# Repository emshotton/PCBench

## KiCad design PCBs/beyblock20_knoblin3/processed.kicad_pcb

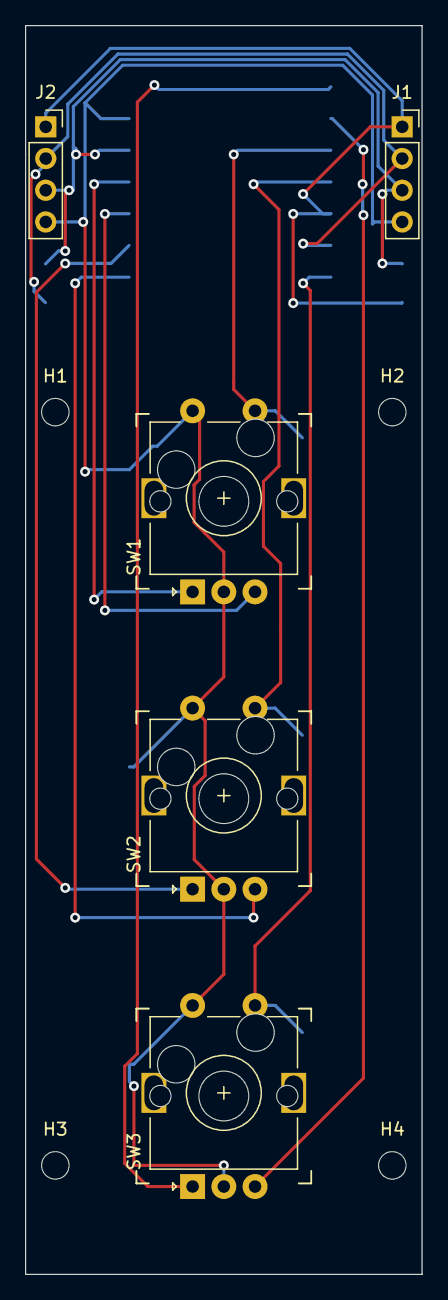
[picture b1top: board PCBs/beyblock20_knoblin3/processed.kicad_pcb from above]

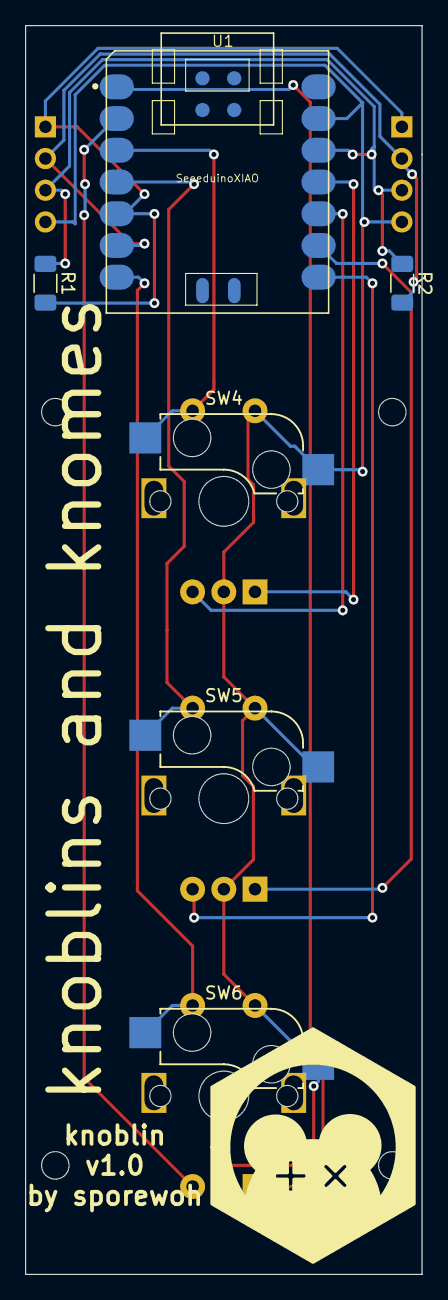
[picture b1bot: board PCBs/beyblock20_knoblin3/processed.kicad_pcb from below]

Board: 2 copper layers, 31.8 x 100.0 mm, 15 parts (3 on the bottom side), 13 nets.

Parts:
H1, H2, H3, H4: MountingHole; MountingHole_2.2mm_M2_DIN965
J1: Conn_01x04_Male; PinSocket_1x04_P2.54mm_Vertical
J2: Conn_01x04_Female; PinSocket_1x04_P2.54mm_Vertical
R1, R2: R; R_1206_3216Metric_Pad1.30x1.75mm_HandSolder
SW1, SW2, SW3: RotaryEncoder_Switch; RotaryEncoder_Alps_EC11E-Switch_Vertical_H20mm
SW4, SW5, SW6: SW_SPST; Kailh_socket_MX
U1: SeeeduinoXIAO; Seeeduino XIAO-MOUDLE14P-2.54-21X17.8MM

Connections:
3v3: J1.3, J2.3, R1.1, R2.1, U1.12 (3V3)
a1: SW1.A, U1.11 (PA6_A10_D10_MOSI)
a2: SW2.A, U1.9 (PA7_A8_D8_SCK)
a3: SW3.A, U1.1 (PA02_A0_D0)
b1: SW1.B, U1.10 (PA5_A9_D9_MISO)
b2: SW2.B, U1.8 (PB09_A7_D7_RX)
b3: SW3.B, U1.2 (PA4_A1_D1)
gnd: J1.4, J2.4, SW1.C, SW1.S2, SW2.C, SW2.S2, SW3.C, SW3.S2, SW4.2 (B), SW5.2 (B), SW6.2 (B), U1.13 (GND)
key1: SW1.S1, SW4.1 (A), U1.3 (PA10_A2_D2)
key2: SW2.S1, SW5.1 (A), U1.4 (PA11_A3_D3)
key3: SW3.S1, SW6.1 (A), U1.7 (PB08_A6_D6_TX)
scl: J1.2, J2.2, R2.2, U1.6 (PA9_A5_D5_SCL)
sda: J1.1, J2.1, R1.2, U1.5 (PA8_A4_D4_SDA)

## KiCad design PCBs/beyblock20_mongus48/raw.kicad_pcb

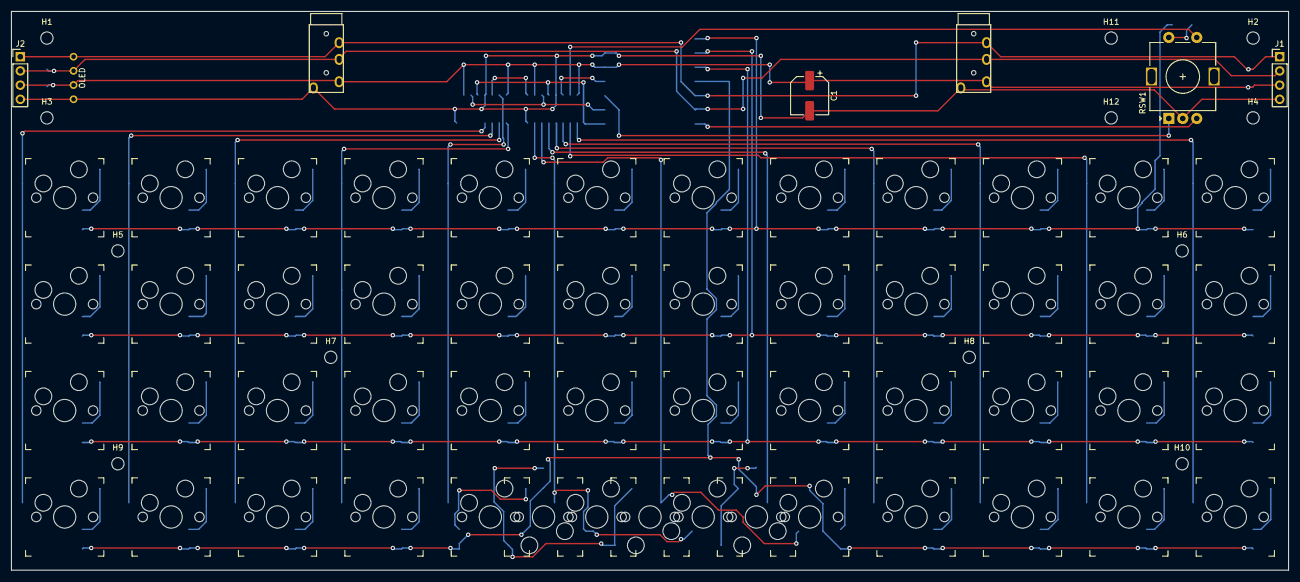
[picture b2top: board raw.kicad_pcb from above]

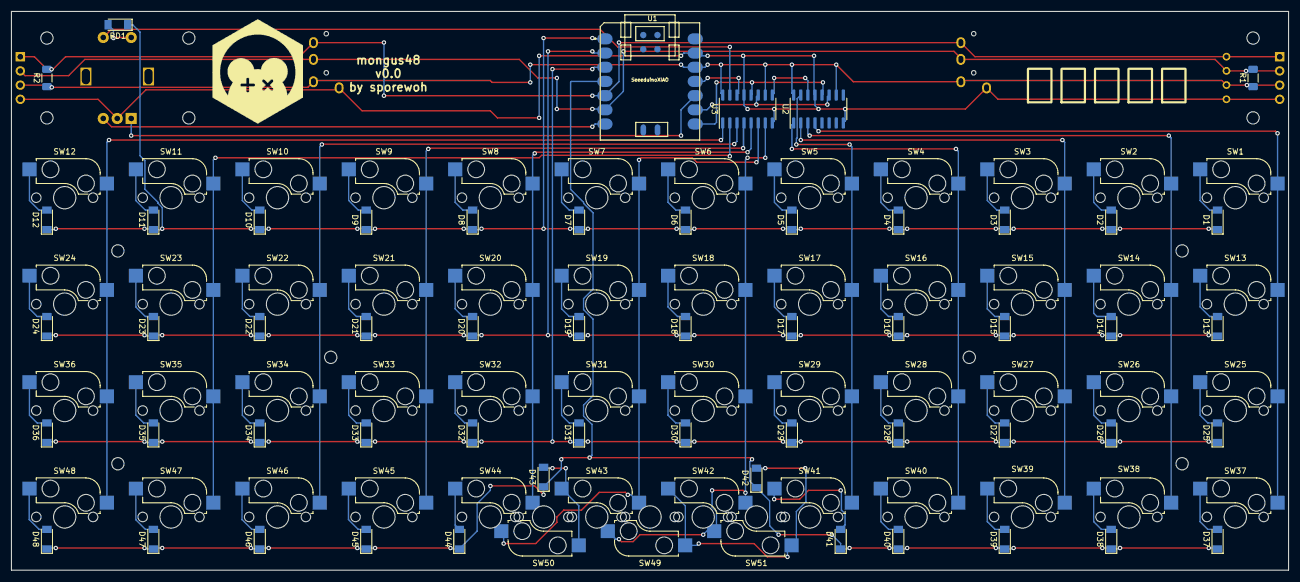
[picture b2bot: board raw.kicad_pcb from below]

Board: 2 copper layers, 228.6 x 100.0 mm, 124 parts (54 on the bottom side), 76 nets.

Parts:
C1: C_Polarized_US; CP_Elec_6.3x7.7
D1, D2, D3, D4, D5, D6, D7, D8, D9, D10, D11, D12, D13, D14, D15, D16, D17, D18, D19, D20, D21, D22, D23, D24, D25, D26, D27, D28, D29, D30, D31, D32, D33, D34, D35, D36, D37, D38, D39, D40, D41, D42, D43, D44, D45, D46, D47, D48: LL4148; D_MiniMELF
H1, H2, H3, H4, H5, H6, H7, H8, H9, H10, H11, H12: MountingHole; MountingHole_2.2mm_M2_DIN965
J1: Conn_01x04_Male; PinHeader_1x04_P2.54mm_Vertical
J2: Conn_01x04_Female; PinHeader_1x04_P2.54mm_Vertical
OL1: OLED; OLED_v2
R1, R2: R; R_1206_3216Metric_Pad1.30x1.75mm_HandSolder
RD1: LL4148; D_MiniMELF
RSW1: RotaryEncoder_Switch; RotaryEncoder_Alps_EC11E-Switch_Vertical_H20mm
SW1, SW2, SW3, SW4, SW5, SW6, SW7, SW8, SW9, SW10, SW11, SW12: locked; Kailh_socket_MX
SW13, SW14, SW15, SW16, SW17, SW18, SW19, SW20, SW21, SW22, SW23, SW24, SW25, SW26, SW27, SW28, SW29, SW30, SW31, SW32, SW33, SW34, SW35, SW36, SW37, SW38, SW39, SW40, SW41, SW42, SW43, SW44, SW45, SW46, SW47, SW48, SW49, SW50, SW51: SW_SPST; Kailh_socket_MX
U1: SeeeduinoXIAO; Seeeduino XIAO-MOUDLE14P-2.54-21X17.8MM
U2, U3: 74HC595; SOP-16_3.9x9.9mm_P1.27mm
U5: TRRS; TRRS-PJ-320A
locked: TRRS; TRRS-PJ-320A

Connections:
3v3: C1.1, J1.3, J2.3, OL1.3 (VCC), R1.1, R2.1, U1.12 (3V3), U2.10 (~SRCLR), U2.16 (VCC), U3.10 (~SRCLR), U3.16 (VCC), U5.2 (TIP), locked.2 (TIP)
unnamed: D1.2 (A), SW1.1 (A)
unnamed: D2.2 (A), SW2.1 (A)
unnamed: D3.2 (A), SW3.1 (A)
unnamed: D4.2 (A), SW4.1 (A)
unnamed: D5.2 (A), SW5.1 (A)
unnamed: D6.2 (A), SW6.1 (A)
unnamed: D7.2 (A), SW7.1 (A)
unnamed: D8.2 (A), SW8.1 (A)
unnamed: D9.2 (A), SW9.1 (A)
unnamed: D10.2 (A), SW10.1 (A)
unnamed: D11.2 (A), SW11.1 (A)
unnamed: D12.2 (A), SW12.1 (A)
unnamed: D13.2 (A), SW13.1 (A)
unnamed: D14.2 (A), SW14.1 (A)
unnamed: D15.2 (A), SW15.1 (A)
unnamed: D16.2 (A), SW16.1 (A)
unnamed: D17.2 (A), SW17.1 (A)
unnamed: D18.2 (A), SW18.1 (A)
unnamed: D19.2 (A), SW19.1 (A)
unnamed: D20.2 (A), SW20.1 (A)
unnamed: D21.2 (A), SW21.1 (A)
unnamed: D22.2 (A), SW22.1 (A)
unnamed: D23.2 (A), SW23.1 (A)
unnamed: D24.2 (A), SW24.1 (A)
unnamed: D25.2 (A), SW25.1 (A)
unnamed: D26.2 (A), SW26.1 (A)
unnamed: D27.2 (A), SW27.1 (A)
unnamed: D28.2 (A), SW28.1 (A)
unnamed: D29.2 (A), SW29.1 (A)
unnamed: D30.2 (A), SW30.1 (A)
unnamed: D31.2 (A), SW31.1 (A)
unnamed: D32.2 (A), SW32.1 (A)
unnamed: D33.2 (A), SW33.1 (A)
unnamed: D34.2 (A), SW34.1 (A)
unnamed: D35.2 (A), SW35.1 (A)
unnamed: D36.2 (A), SW36.1 (A)
unnamed: D37.2 (A), SW37.1 (A)
unnamed: D38.2 (A), SW38.1 (A)
unnamed: D39.2 (A), SW39.1 (A)
unnamed: D40.2 (A), SW40.1 (A)
unnamed: D41.2 (A), SW41.1 (A)
unnamed: D42.2 (A), SW42.1 (A), SW49.1 (A), SW51.1 (A)
unnamed: D43.2 (A), SW43.1 (A), SW50.1 (A)
unnamed: D44.2 (A), SW44.1 (A)
unnamed: D45.2 (A), SW45.1 (A)
unnamed: D46.2 (A), SW46.1 (A)
unnamed: D47.2 (A), SW47.1 (A)
unnamed: D48.2 (A), SW48.1 (A)
unnamed: RD1.2 (A), RSW1.S2
unnamed: U2.14 (SER), U3.9 (QH')
col0: RSW1.S1, U3.15 (QA)
col1: SW12.2 (B), SW24.2 (B), SW36.2 (B), SW48.2 (B), U3.1 (QB)
col2: SW11.2 (B), SW23.2 (B), SW35.2 (B), SW47.2 (B), U3.2 (QC)
col3: SW10.2 (B), SW22.2 (B), SW34.2 (B), SW46.2 (B), U3.3 (QD)
col4: SW9.2 (B), SW21.2 (B), SW33.2 (B), SW45.2 (B), U3.4 (QE)
col5: SW8.2 (B), SW20.2 (B), SW32.2 (B), SW44.2 (B), U3.5 (QF)
col6: SW7.2 (B), SW19.2 (B), SW31.2 (B), SW43.2 (B), SW50.2 (B), U3.6 (QG)
col7: SW6.2 (B), SW18.2 (B), SW30.2 (B), SW42.2 (B), SW49.2 (B), SW51.2 (B), U3.7 (QH)
col8: SW5.2 (B), SW17.2 (B), SW29.2 (B), SW41.2 (B), U2.15 (QA)
col9: SW4.2 (B), SW16.2 (B), SW28.2 (B), SW40.2 (B), U2.1 (QB)
col10: SW3.2 (B), SW15.2 (B), SW27.2 (B), SW39.2 (B), U2.2 (QC)
col11: SW2.2 (B), SW14.2 (B), SW26.2 (B), SW38.2 (B), U2.3 (QD)
col12: SW1.2 (B), SW13.2 (B), SW25.2 (B), SW37.2 (B), U2.4 (QE)
gnd: C1.2, J1.4, J2.4, OL1.4 (GND), RSW1.C, U1.13 (GND), U2.8 (GND), U2.13 (~OE), U3.8 (GND), U3.13 (~OE), U5.1 (SLEEVE), locked.1 (SLEEVE)
io_cs: U1.8 (PB09_A7_D7_RX), U2.12 (RCLK), U3.12 (RCLK)
mosi: U1.11 (PA6_A10_D10_MOSI), U3.14 (SER)
pad_a: RSW1.A, U1.10 (PA5_A9_D9_MISO)
pad_b: RSW1.B, U1.7 (PB08_A6_D6_TX)
row0: D1.1 (K), D2.1 (K), D3.1 (K), D4.1 (K), D5.1 (K), D6.1 (K), D7.1 (K), D8.1 (K), D9.1 (K), D10.1 (K), D11.1 (K), D12.1 (K), RD1.1 (K), U1.1 (PA02_A0_D0)
row1: D13.1 (K), D14.1 (K), D15.1 (K), D16.1 (K), D17.1 (K), D18.1 (K), D19.1 (K), D20.1 (K), D21.1 (K), D22.1 (K), D23.1 (K), D24.1 (K), U1.2 (PA4_A1_D1)
row2: D25.1 (K), D26.1 (K), D27.1 (K), D28.1 (K), D29.1 (K), D30.1 (K), D31.1 (K), D32.1 (K), D33.1 (K), D34.1 (K), D35.1 (K), D36.1 (K), U1.3 (PA10_A2_D2)
row3: D37.1 (K), D38.1 (K), D39.1 (K), D40.1 (K), D41.1 (K), D42.1 (K), D43.1 (K), D44.1 (K), D45.1 (K), D46.1 (K), D47.1 (K), D48.1 (K), U1.4 (PA11_A3_D3)
sck: U1.9 (PA7_A8_D8_SCK), U2.11 (SRCLK), U3.11 (SRCLK)
scl: J1.2, J2.2, OL1.2 (SCL), R1.2, U1.6 (PA9_A5_D5_SCL), U5.3 (RING1), locked.3 (RING1)
sda: J1.1, J2.1, OL1.1 (SDA), R2.2, U1.5 (PA8_A4_D4_SDA), U5.4 (RING2), locked.4 (RING2)

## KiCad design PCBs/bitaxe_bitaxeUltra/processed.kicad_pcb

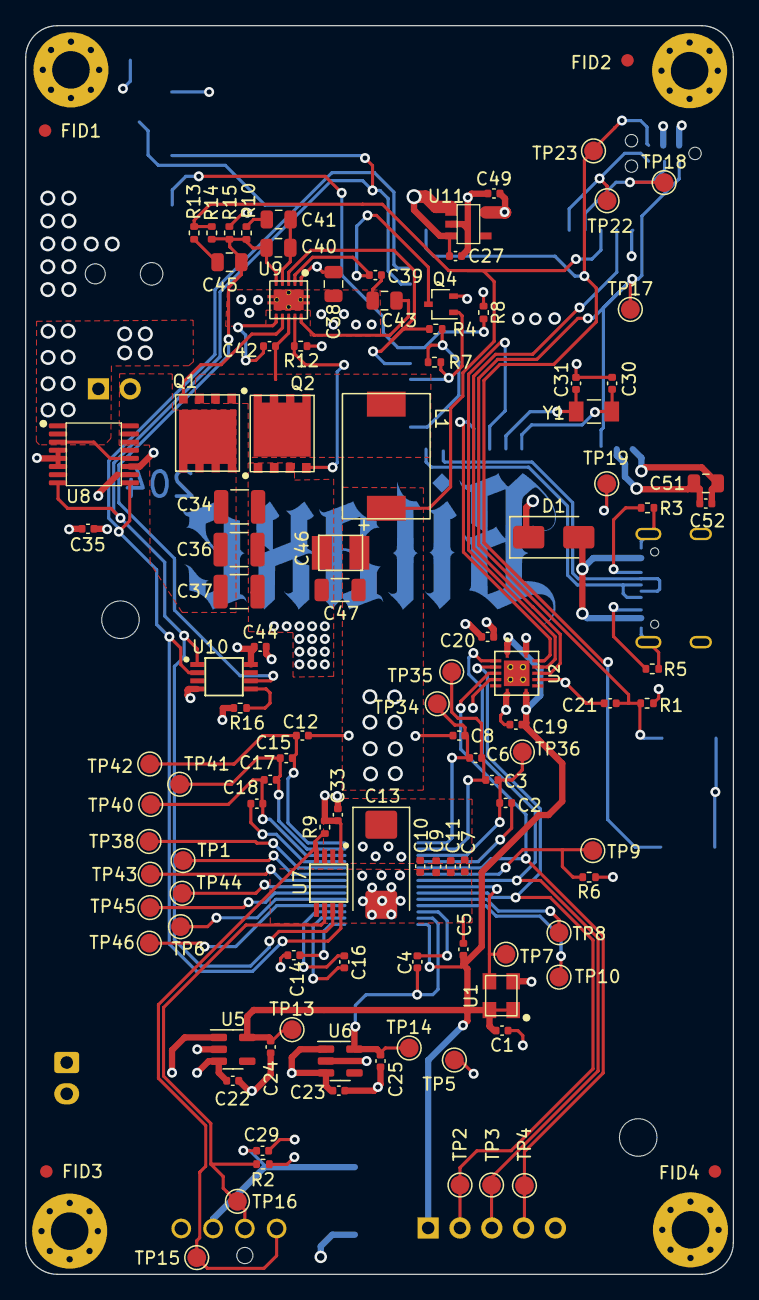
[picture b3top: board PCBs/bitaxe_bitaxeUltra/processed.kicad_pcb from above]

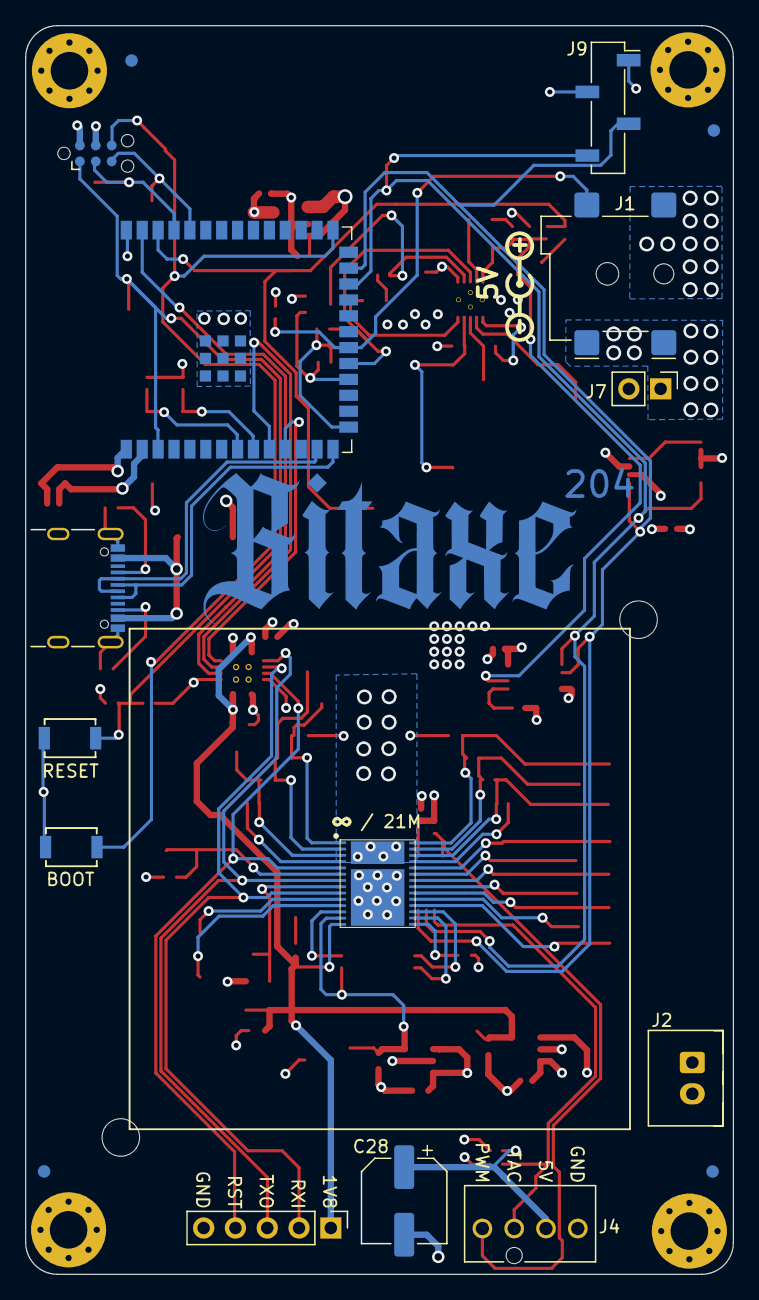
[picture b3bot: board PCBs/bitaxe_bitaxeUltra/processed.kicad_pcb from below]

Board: 4 copper layers, 56.5 x 99.8 mm, 135 parts (18 on the bottom side), 61 nets.

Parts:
C1, C7, C9, C19, C20, C29, C33, C42, C52: 0.1uF; C_0402_1005Metric
C2, C3, C4, C5, C6, C8, C10, C11, C12, C14, C15, C16, C17, C18, C21, C22, C23, C24, C25, C27, C35, C44, C49: 1uF; C_0402_1005Metric
C13: 330uF; CP_EIA-7343-31_Kemet-D_Pad2.25x2.55mm_HandSolder
C28: 220uF; CP_Elec_6.3x7.7
C30, C31: 6.8pF; C_0402_1005Metric
C34, C36, C37: 47uF; C_1210_3225Metric
C38: 1uF; C_0805_2012Metric
C39: 3.3nF; C_0402_1005Metric
C40: 180pF; C_0805_2012Metric
C41: 1.5nF; C_0805_2012Metric
C43, C51: 10uF; C_0805_2012Metric
C45: 470pF; C_0805_2012Metric
C46: 220uF; CAP_2R5TPE220MAFB
C47: 100uF; C_1206_3216Metric
D1: SS310; D_SMA
FID1, FID2, FID3, FID4, FID5, FID6, FID7, FID8: Fiducial; Fiducial_1mm_Mask2mm
H5, H6: MountingHole; MountingHole_3.5mm
H7, H8, H9, H10: MountingHole_Pad; MountingHole_3mm_Pad_Via
J1: 54-00164; BarrelJack_Wuerth_694106106102_2.0x5.5mm
J2: Conn_01x02; JST_XH_B2B-XH-A_1x02_P2.50mm_Vertical
J3: Conn_01x05; PinHeader_1x05_P2.54mm_Vertical
J4: Conn_01x04; 470531000
J5: TC2030-IDC; Tag-Connect_TC2030-IDC-NL_2x03_P1.27mm_Vertical
J7: Conn_01x02; PinHeader_1x02_P2.54mm_Vertical
J8: USB_C_Receptacle_USB2.0; USB_C_Receptacle_GCT_USB4105-xx-A_16P_TopMnt_Horizontal
J9: Conn_01x04; PinSocket_1x04_P2.54mm_Vertical_SMD_Pin1Right
L1: 150nH; FP1005R1-R15-R
Q1, Q2: CSD17311Q5
Q4: 2N7002K; SOT-323_SC-70
R1, R4, R6, R7, R9: 10k; R_0402_1005Metric
R2: 5.6k; R_0402_1005Metric
R3, R5: 5.1k; R_0402_1005Metric
R8: 1M; R_0402_1005Metric
R10: 3.83k; R_0402_1005Metric
R12: 4.12k; R_0402_1005Metric
R13: 1.33k; R_0402_1005Metric
R14: 4.99k; R_0402_1005Metric
R15: 3.32k; R_0402_1005Metric
R16: 80.6k; R_0402_1005Metric
SW1, SW2: GT-TC029B-H025-L1N; SW_CS1213AGF260_CRS
TP1, TP2, TP3, TP4, TP5, TP6, TP7, TP8, TP9, TP10, TP13, TP14, TP15, TP16, TP17, TP18, TP19, TP22, TP23, TP34, TP35, TP36, TP38, TP40, TP41, TP42, TP43, TP44, TP45, TP46: TestPoint; TestPoint_Pad_D1.5mm
U1: 25MHz; O 25,0-JO32-B-1V3-1-T1-LF
U2: TXB0104RGYR; TXB0104
U3: polarity
U5: MCP1824T-1802E; SOT-23-5
U6: MCP1824T-0802E; SOT-23-5
U7: EMC2101; TSSOP-8_3x3mm_P0.65mm
U8: INA260; TSSOP-16_4.4x5mm_P0.65mm
U9: TPS40305
U10: DS4432U+; TSSOP-8_3x3mm_P0.65mm
U11: RT9080-33GJ5
U12: ESP32-S3-WROOM-1
U14: BM1366_mode1; BM1366
Y1: 32.768kHz; SC32S-7PF20PPM

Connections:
/3V3: C20.1, C33.1, C35.1, C44.1, C49.1, C51.1, C52.1, J5.2, J9.2, R1.1, R2.2, R4.1, R7.1, R8.1, R9.2, TP19.1, U2.14 (VCCB), U7.1 (VDD), U8.10 (VS), U10.8 (VCC), U11.5 (VOUT), U12.2 (3V3), U12.15 (GPIO3/TOUCH3/ADC1_CH2*)
/5V: C22.1, C23.1, C27.1, C28.1, C29.1, C34.1, C36.1, C37.1, C38.1, D1.1, J2.2, J4.2, J7.2, Q1.5 (D), U5.1 (VIN), U5.3 (EN), U6.1 (VIN), U6.3 (EN), U8.14 (IN-), U8.15 (IN-), U8.16 (IN-), U9.1 (VDD), U11.1 (VIN), U11.3 (EN)
/BM1366/0V8: C4.1, C25.1, TP14.1, U6.5 (VOUT), U14.13 (VDDIO_08_0)
/BM1366/1V8: C1.2, C5.1, C19.1, C24.1, J3.1, TP13.1, U1.1 (EN), U1.4 (VIN), U2.1 (VCCA), U2.8 (OE), U5.5 (VOUT), U14.14 (VDDIO_18_0)
/BM1366/ADDR0: TP8.1, U14.10 (ADDR0)
/BM1366/ADDR1: TP10.1, U14.11 (ADDR1)
/BM1366/BI: R6.2, TP9.1, U14.6 (BI)
/BM1366/BO: TP1.1, U14.23 (BO)
/BM1366/CI: J3.2, TP2.1, U2.3 (A2), U14.9 (CI)
/BM1366/CLKI: TP7.1, U1.3 (OUT), U14.8 (CLKI)
/BM1366/CLKO: TP44.1, U14.21 (CLKO)
/BM1366/CO: TP45.1, U14.20 (CO)
/BM1366/INV_CLKO: TP6.1, U14.19 (INV_CLKO)
/BM1366/NRSTO: TP38.1, U14.24 (NRSTO)
/BM1366/PIN_MODE: TP46.1, U14.18 (PIN_MODE)
/BM1366/RI: TP43.1, U14.22 (RI)
/BM1366/RO: J3.3, TP3.1, U2.2 (A1), U14.7 (RO)
/BM1366/RST_N: J3.4, TP4.1, U2.4 (A3), U14.5 (NRSTI)
/BM1366/VDD1_0: C6.2, C8.1, TP34.1, U14.1 (VDD1_0)
/BM1366/VDD1_1: C12.2, C15.1, TP42.1, U14.28 (VDD1_1)
/BM1366/VDD2_0: C3.2, C6.1, TP35.1, U14.2 (VDD2_0)
/BM1366/VDD2_1: C15.2, C17.1, TP41.1, U14.27 (VDD2_1)
/BM1366/VDD3_0: C2.2, C3.1, TP36.1, U14.3 (VDD3_0)
/BM1366/VDD3_1: C17.2, C18.1, TP40.1, U14.26 (VDD3_1)
/ESP32/EN: C21.1, J5.1, R1.2, SW1.2, TP17.1, U12.3 (EN)
/ESP32/IO0: J5.6, SW2.2, TP23.1, U12.27 (GPIO0/BOOT*)
/ESP32/PWR_EN: Q4.1 (G), R7.2, U12.18 (GPIO10/TOUCH10/ADC1_CH9/FSPICS0/FSPIIO4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)
/ESP32/P_RX: J5.5, TP22.1, U12.36 (U0RXD/GPIO44/CLK_OUT2)
/ESP32/P_TX: J5.3, TP18.1, U12.37 (U0TXD/GPIO43/CLK_OUT1)
/ESP32/XIN32: C30.1, U12.8 (GPIO15/U0RTS/ADC2_CH4/XTAL_32K_P), Y1.1
/ESP32/XOUT32: C31.1, U12.9 (GPIO16/U0CTS/ADC2_CH5/XTAL_32K_NH5), Y1.2
/Fan/FAN_PWM: J4.4, R9.1, TP15.1, U7.4 (FAN)
/Fan/FAN_TACH: J4.3, R2.1, TP16.1, U7.6 (ALERT/TACH)
/PLUG_SENSE: J1.3, R8.2, U12.20 (GPIO12/TOUCH12/ADC2_CH1/FSPICLK/FSPIIO6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)
/Power/OUT0: C40.2, C45.2, R10.2, R14.2, R15.1, U9.5 (FB), U10.6 (OUT0)
/Power/PGOOD: R4.2, U9.3 (PGOOD), U12.19 (GPIO11/TOUCH11/ADC2_CH0/FSPID/FSPIIO5/S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)
/Power/SW: C42.2, L1.1, Q1.1, Q1.2, Q1.3 (S), Q2.5 (D), U9.8 (SW)
/Power/VIN: J1.1, J7.1, U8.1 (IN+), U8.2 (IN+), U8.3 (IN+), U8.12 (VBUS)
/RST: U2.11 (B3), U12.39 (GPIO1/TOUCH1/ADC1_CH0)
/RX: U2.13 (B1), U12.11 (GPIO18/U1RXD/ADC2_CH7/CLK_OUT3)
/SCL: J9.3, U7.8 (SMCLK), U8.9 (SCL), U10.2 (SCL), U12.25 (GPIO48/SPICLK_N/SUBSPICLK_N_DIFF)
/SDA: J9.4, U7.7 (SMDATA), U8.8 (SDA), U10.1 (SDA), U12.24 (GPIO47/SPICLK_P/SUBSPICLK_P_DIFF)
/TX: U2.12 (B2), U12.10 (GPIO17/U1TXD/ADC2_CH6)
/VDD: C7.1, C8.2, C9.1, C10.1, C11.1, C12.1, C13.1, C46.1, C47.1, L1.2, R13.1, R14.1, U12.38 (GPIO2/TOUCH2/ADC1_CH1), U14.29 (VDD)
GND: C1.1, C2.1, C4.2, C5.2, C7.2, C9.2, C10.2, C11.2, C13.2, C14.2, C16.2, C18.2, C19.2, C20.2, C21.2, C22.2, C23.2, C24.2, C25.2, C27.2, C28.2, C29.2, C30.2, C31.2, C33.2, C34.2, C35.2, C36.2, C37.2, C38.2, C39.2, C43.2, C44.2, C46.2, C47.2, C49.2, C51.2, C52.2, H7.1, H8.1, H9.1, H10.1, J1.2, J2.1, J3.5, J4.1, J5.4, J8.A1 (GND), J8.A12 (GND), J8.B1 (GND), J8.B12 (GND), J8.S1 (SHIELD), J9.1, Q2.1, Q2.2, Q2.3 (S), Q4.2 (S), R3.1, R5.1, R6.1, R12.2, R15.2, R16.2, SW1.1, SW2.1, TP5.1, U1.2 (GND), U2.5 (A4), U2.7 (GND), U2.10 (B4), U2.15 (GND), U2.16 (GND), U2.17 (GND), U2.18 (GND), U2.19 (GND), U5.2 (GND), U6.2 (GND), U7.5 (GND), U8.4 (A1), U8.5 (A0), U8.6 (GND), U8.11 (GND), U9.11 (GND), U10.4 (GND), U11.2 (GND), U12.1 (GND), U12.40 (GND), U12.41 (GND), U14.4 (VSS), U14.12 (PLL_VSS), U14.17 (VSS), U14.25 (VSS), U14.30 (VSS)
unnamed: C41.2, R10.1
unnamed: C45.1, R13.2
unnamed: D1.2, J8.A4 (VBUS), J8.A9 (VBUS), J8.B4 (VBUS), J8.B9 (VBUS)
unnamed: J8.A5 (CC1), R3.2
unnamed: J8.B5 (CC2), R5.2
unnamed: Q1.4 (G), U9.7 (HDRV)
unnamed: Q2.4 (G), R12.1, U9.9 (LDRV)
unnamed: C39.1, Q4.3 (D), U9.2 (EN/SS)
unnamed: C42.1, U9.6 (BOOT)
unnamed: C43.1, U9.10 (BP)
unnamed: C40.1, C41.1, U9.4 (COMP)
unnamed: R16.1, U10.5 (FS0)
unnamed: J8.A7 (D-), J8.B7 (D-), U12.13 (GPIO19/U1RTS/ADC2_CH8/CLK_OUT2/USB_D-)
unnamed: J8.A6 (D+), J8.B6 (D+), U12.14 (GPIO20/U1CTS/ADC2_CH9/CLK_OUT1/USB_D+)
unnamed: C16.1, U14.16 (VDDIO_08_1)
unnamed: C14.1, U14.15 (VDDIO_18_1)

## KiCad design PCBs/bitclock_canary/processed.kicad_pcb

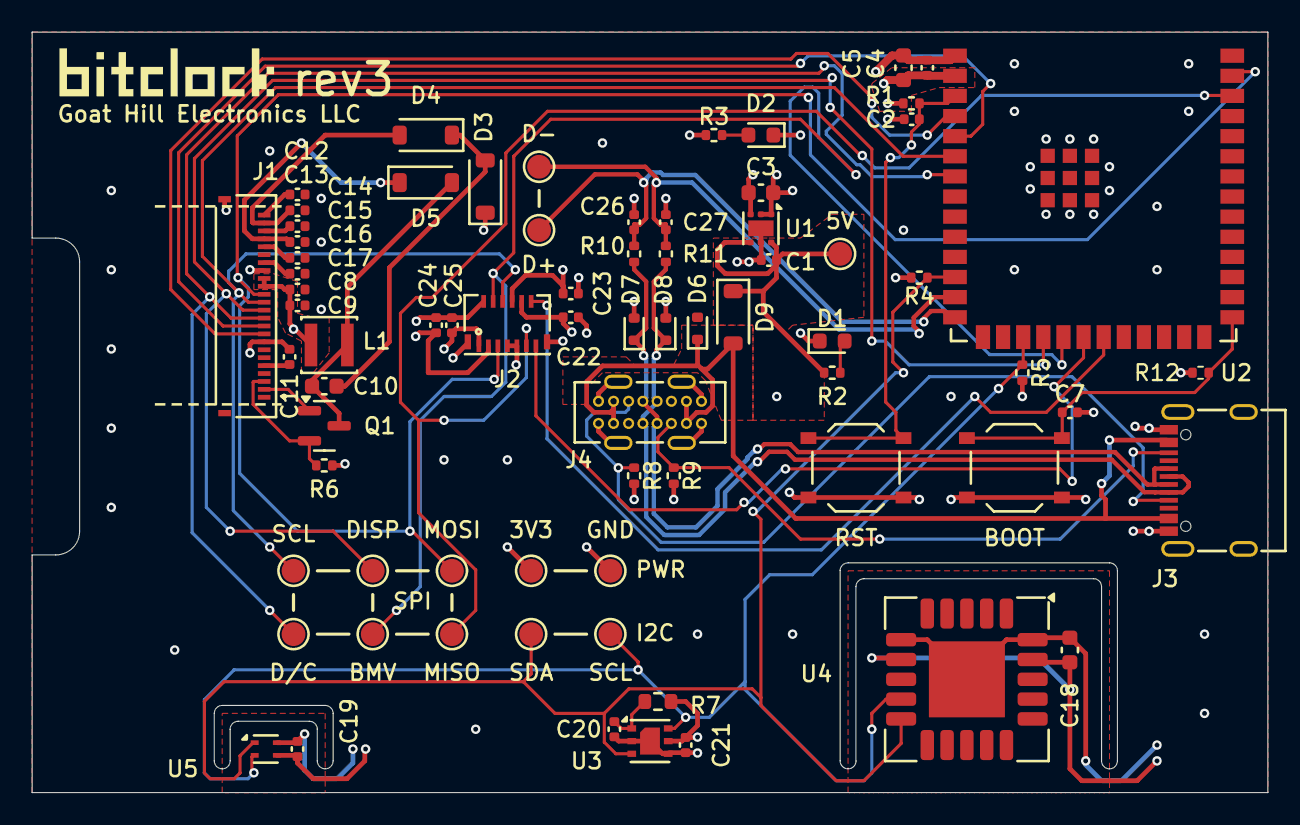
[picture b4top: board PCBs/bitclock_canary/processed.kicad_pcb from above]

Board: 4 copper layers, 78.0 x 48.0 mm, 74 parts (1 on the bottom side), 38 nets.

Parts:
C1, C2, C9, C11, C12, C13, C14, C15, C16, C17, C20, C21, C22, C23, C24, C25: 1µF; C_0402_1005Metric
C3: 2.2µF; C_0603_1608Metric
C4, C8, C19: 100nF; C_0402_1005Metric
C5, C18: 10µF; C_0603_1608Metric
C7: 10pF; C_0402_1005Metric
C10: 4.7µF; C_0603_1608Metric
C26, C27: 22pF; C_0402_1005Metric
D1: KT-0603R; LED_0603_1608Metric
D2: 19-213/Y2C-CQ2R2L/3T(CY); LED_0603_1608Metric
D3, D4, D5, D9: 1N5819HW-7-F; D_SOD-123
D6, D7, D8: LESD5D5.0CT1G; D_SOD-523
EINK1: EInk_Display_2.71_E2271KS0C1
J1: FH34SRJ-24S-0.5SH; HRS_FH34SRJ-24S-0.5SH_99_
J2: ECT818001568; FPC-SMD_ECT818001568
J3: TYPE-C16PIN; USB-C-SMD_TYPE-C16PIN
J4: TYPE-C 16PLC-H10.0; TYPE-C-TH_16PLC-H10.0
L1: 600mA 10uH ±20% SPH3010H100MT; L_Sunlord_SWPA3010S
Q1: AO3400A; SOT-23
R1, R12: 10kΩ; R_0402_1005Metric
R2: 1k; R_0402_1005Metric
R3: 470R; R_0402_1005Metric
R4, R5, R8, R9: 5.1kΩ; R_0402_1005Metric
R6: 470mΩ; R_0402_1005Metric
R7: 4.7Ω; R_0603_1608Metric
R10, R11: 0Ω; R_0402_1005Metric
SW1, SW2: SW_Push; SW_Push_1P1T_XKB_TS-1187A
TP1, TP2, TP3, TP4, TP5, TP6, TP7, TP8, TP9, TP10, TP11, TP12, TP13: TestPoint; TestPoint_Pad_D1.5mm
U1: TLV76733DRVT; WSON-6-1EP_2x2mm_P0.65mm_EP1x1.6mm
U2: ESP32-S3-WROOM-1-N8; ESP32-S3-WROOM-1
U3: SGP41-D-R4; XDCR_SGP41-D-R4
U4: SCD40-D-R2; Sensirion_SCD4x-1EP_10.1x10.1mm_P1.25mm_EP4.8x4.8mm
U5: SHT40-AD1B-R2; Sensirion_DFN-4_1.5x1.5mm_P0.8mm_SHT4x_NoCentralPad

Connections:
+3.3V: C3.2, C4.1, C5.1, C8.1, C9.1, C18.1, C19.2, C21.1, C22.2, C23.2, C24.2, C25.2, J1.15 (VDDIO), J1.16 (VDD), J2.1 (VDDL), J2.3 (VDDA), J2.8 (VDDIO), J2.10 (VDDD), L1.1, R1.1, R3.1, R4.2, R5.2, R7.1, R12.2, TP2.1, U1.1 (OUT), U1.2 (SNS), U2.2 (3V3), U3.5 (VDDH), U4.7 (VDD), U4.19 (VDD), U5.3 (VDD)
+5V: C1.2, D9.1 (K), R2.1, TP1.1, U1.4 (EN), U1.6 (IN)
/BMV_IRQ1: J2.13 (IRQ1), U2.20 (GPIO12/TOUCH12/ADC2_CH1/FSPICLK/FSPIIO6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)
/BMV_IRQ2: J2.12 (IRQ2), U2.21 (GPIO13/TOUCH13/ADC2_CH2/FSPIQ/FSPIIO7/S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)
/BOOT: C7.1, R12.1, SW2.1, U2.27 (GPIO0/BOOT)
/CHIP_EN: C2.1, R1.2, SW1.1, U2.3 (EN)
/D+: C26.1, R10.2, TP6.1, U2.14 (GPIO20/U1CTS/ADC2_CH9/CLK_OUT1/USB_D+)
/D-: C27.1, R11.2, TP7.1, U2.13 (GPIO19/U1RTS/ADC2_CH8/CLK_OUT2/USB_D-)
/D_BUSY_N: J1.9 (BUSY_N), U2.4 (GPIO4/TOUCH4/ADC1_CH3)
/D_DC: J1.11 (DC), TP10.1, U2.7 (GPIO7/TOUCH7/ADC1_CH6)
/D_RST_N: J1.10 (RST_N), U2.5 (GPIO5/TOUCH5/ADC1_CH4)
/Display Port/D_GDR: J1.2 (GDR), Q1.1 (G)
/Display Port/D_RESE: J1.3 (RESE), Q1.2 (S), R6.1
/Display Port/D_VCOM: C12.1, J1.24 (VCOM)
/Display Port/D_VDDD: C17.1, J1.18 (VDDD)
/Display Port/D_VDH: C16.1, J1.20 (VDH)
/Display Port/D_VDHR: C11.1, J1.5 (VDHR)
/Display Port/D_VDL: C14.1, J1.22 (VDL)
/Display Port/D_VGH: C15.1, D5.1 (K), J1.21 (VGH)
/Display Port/D_VGH_BD: C10.1, D5.2 (A), L1.2, Q1.3 (D)
/Display Port/D_VGL: C13.1, D4.2 (A), J1.23 (VGL)
/Display Port/D_VGL_PD: C10.2, D3.2 (A), D4.1 (K)
/I2C_SCL: R5.1, TP5.1, U2.17 (GPIO9/TOUCH9/ADC1_CH8/FSPIHD/SUBSPIHD), U3.6 (SCL), U4.9 (SCL), U5.2 (SCL)
/I2C_SDA: R4.1, TP4.1, U2.12 (GPIO8/TOUCH8/ADC1_CH7/SUBSPICS1), U3.3 (SDA), U4.10 (SDA), U5.1 (SDA)
/LED_R: D1.2 (A), R2.2
/LED_Y: D2.2 (A), R3.2
/SPI_CS_BMV: J2.4 (CSB), TP8.1, U2.19 (GPIO11/TOUCH11/ADC2_CH0/FSPID/FSPIIO5/S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)
/SPI_CS_DISP: J1.12 (CSB), TP9.1, U2.18 (GPIO10/TOUCH10/ADC1_CH9/FSPICS0/FSPIIO4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)
/SPI_MISO: J2.11 (MISO), TP13.1, U2.38 (GPIO2/TOUCH2/ADC1_CH1)
/SPI_MOSI: J1.14 (SDA), J2.5 (MOSI), TP12.1, U2.39 (GPIO1/TOUCH1/ADC1_CH0)
/SPI_SCL: J1.13 (SCL), J2.6 (SCK), TP11.1, U2.6 (GPIO6/TOUCH6/ADC1_CH5)
/Sensors/SGP4X_VDD: C20.1, R7.2, U3.1 (VDD)
/USB/CC1: J3.A5 (CC1), J4.A5 (CC1), R8.1
/USB/CC2: J3.B5 (CC2), J4.B5 (CC2), R9.1
/USB/USB_D+: D7.1 (A1), J3.A6 (DP1), J3.B6 (DP2), J4.A6 (D+), J4.B6 (D+), R10.1
/USB/USB_D-: D8.1 (A1), J3.A7 (DN1), J3.B7 (DN2), J4.A7 (D-), J4.B7 (D-), R11.1
GND: C1.1, C2.2, C3.1, C4.2, C5.2, C7.2, C8.2, C9.2, C11.2, C12.2, C13.2, C14.2, C15.2, C16.2, C17.2, C18.2, C19.1, C20.2, C21.2, C22.1, C23.1, C24.1, C25.1, C26.2, C27.2, D1.1 (K), D2.1 (K), D3.1 (K), D6.2 (A2), D7.2 (A2), D8.2 (A2), J1.8 (BS), J1.17 (GND), J1.S (SHIELD), J2.2 (VSSA), J2.7 (PS), J2.9 (VSSD), J2.14 (SHELL), J2.15 (SHELL), J3.1 (SHELL), J3.2 (SHELL), J3.3 (SHELL), J3.4 (SHELL), J3.A1B12 (GND), J3.B1A12 (GND), J4.A1 (GND), J4.A12 (GND), J4.B1 (GND), J4.B12 (GND), J4.S1 (SHIELD), R6.2, R8.2, R9.2, SW1.2, SW2.2, TP3.1, U1.3 (GND), U1.5 (GND), U1.7 (PAD), U2.1 (GND), U2.40 (GND), U2.41 (GND), U3.2 (VSS), U3.4 (N/A), U3.7 (EXP), U4.6 (GND), U4.20 (GND), U4.21 (GND), U5.4 (VSS)
VBUS: D6.1 (A1), D9.2 (A), J3.A4B9 (VBUS), J3.B4A9 (VBUS), J4.A4 (VBUS), J4.A9 (VBUS), J4.B4 (VBUS), J4.B9 (VBUS)

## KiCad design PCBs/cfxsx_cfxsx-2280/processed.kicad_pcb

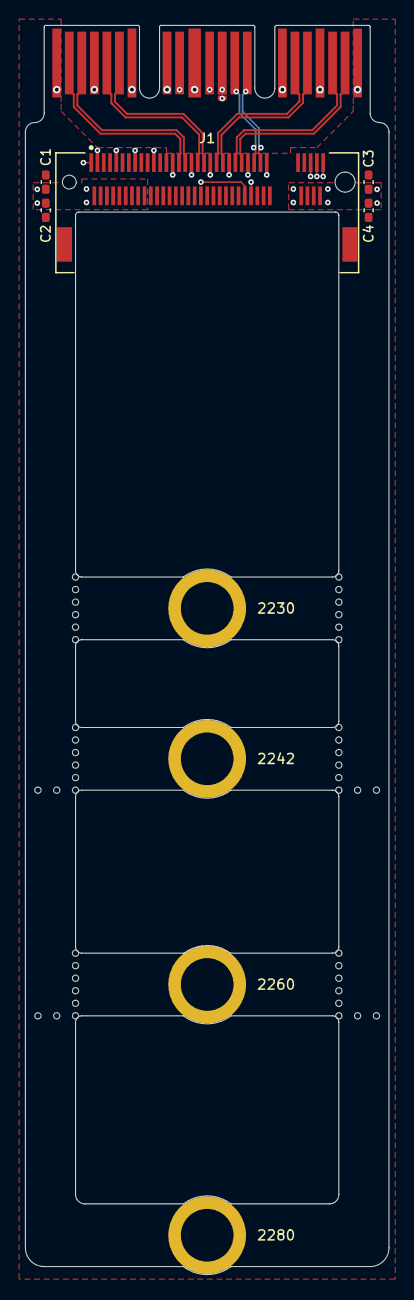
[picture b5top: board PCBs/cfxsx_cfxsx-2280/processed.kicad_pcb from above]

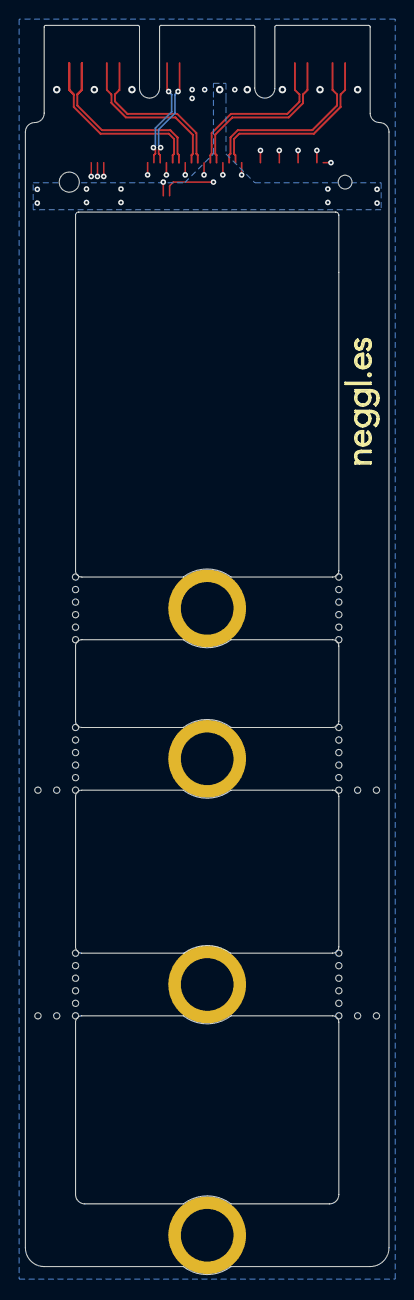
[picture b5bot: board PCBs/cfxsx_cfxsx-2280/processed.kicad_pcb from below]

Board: 4 copper layers, 29.0 x 99.6 mm, 12 parts (5 on the bottom side), 15 nets.

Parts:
C1, C3: 0.1u; C_0402_1005Metric_Pad0.74x0.62mm_HandSolder
C2, C4: 10u; C_0402_1005Metric_Pad0.74x0.62mm_HandSolder
J1: M.2 NGFF; AMP_MDT180xxx001_NGFF-KeyM
JP1: F_INS; SolderJumper-2_P0.6mm_Open_RoundedPad1.0x1.5mm
MP1: 2280; MountingHole_NGFF_4.2mm_Pad_TopBottom
MP1#2: 2260; MountingHole_NGFF_4.2mm_Pad_TopBottom
MP1#3: 2230; MountingHole_NGFF_4.2mm_Pad_TopBottom
MP2: 2242; MountingHole_NGFF_4.2mm_Pad_TopBottom
PC1: CFexpress; CFExpress_Media
SYM1: logo; neggle-logo-0.12

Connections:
+3V3: C1.1, C2.1, C3.1, C4.1, J1.2, J1.4, J1.12, J1.14, J1.16, J1.18, J1.70, J1.72, J1.74, PC1.10
/PER0_N: J1.41, PC1.16
/PER0_P: J1.43, PC1.17
/PER1_N: J1.29, PC1.2
/PER1_P: J1.31, PC1.3
/PET0_N: J1.47, PC1.19
/PET0_P: J1.49, PC1.20
/PET1_N: J1.35, PC1.5
/PET1_P: J1.37, PC1.6
/REFCLK+: J1.55, PC1.14
/REFCLK-: J1.53, PC1.13
/~CLK_REQ: J1.52, PC1.11
/~INS: J1.1, JP1.2, PC1.12
/~PERST: J1.50, PC1.9
GND: C1.2, C2.2, C3.2, C4.2, J1.3, J1.9, J1.15, J1.21, J1.27, J1.33, J1.39, J1.45, J1.51, J1.57, J1.71, J1.73, J1.75, J1.MP, JP1.1, MP1.1, MP1#2.1, MP1#3.1, MP2.1, PC1.1, PC1.4, PC1.7, PC1.8, PC1.15, PC1.18, PC1.21

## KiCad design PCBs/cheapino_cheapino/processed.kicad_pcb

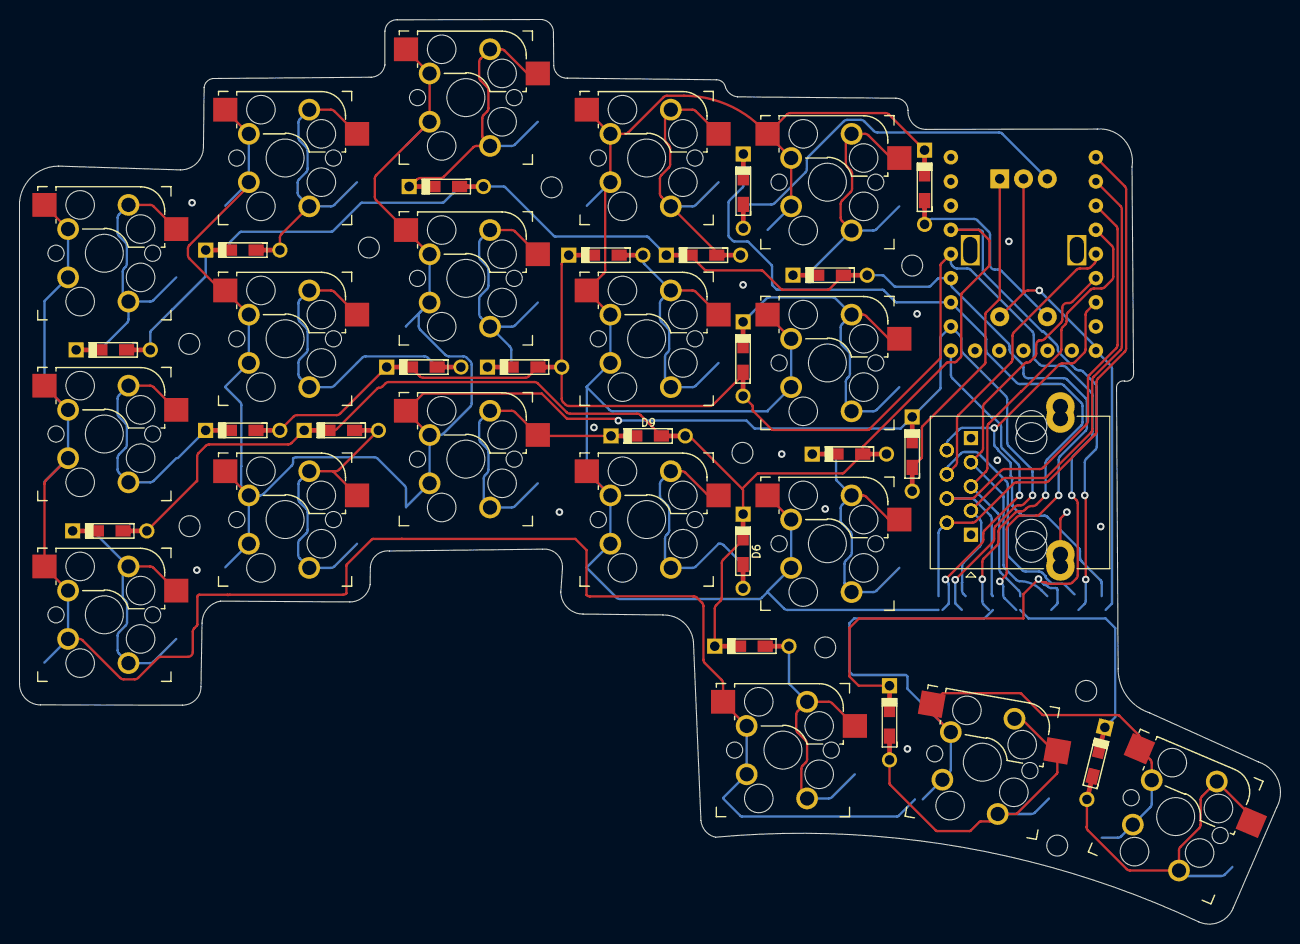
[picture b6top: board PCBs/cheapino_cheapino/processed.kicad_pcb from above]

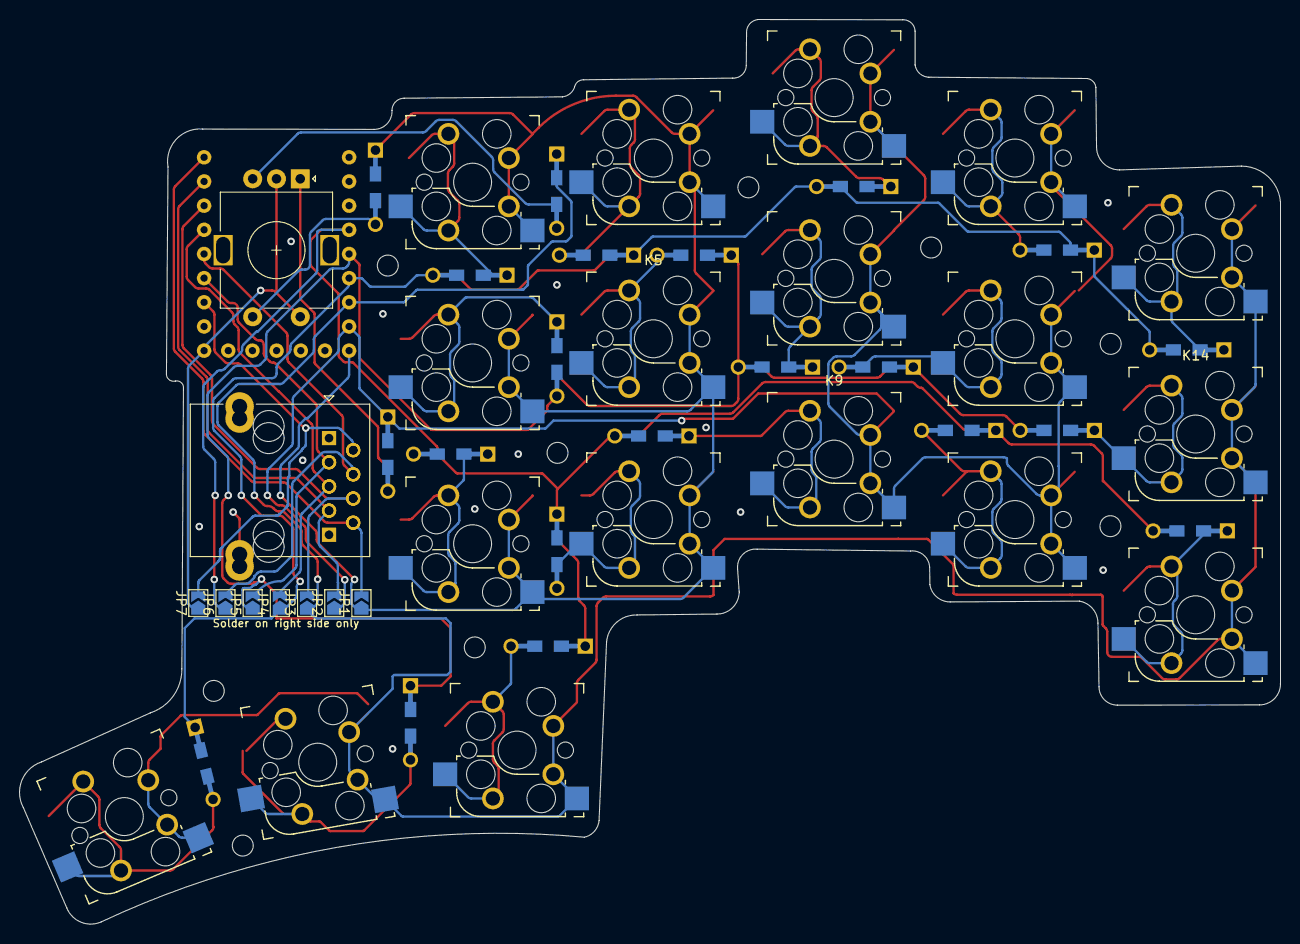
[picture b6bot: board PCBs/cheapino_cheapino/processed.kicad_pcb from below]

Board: 2 copper layers, 132.5 x 95.1 mm, 50 parts (9 on the bottom side), 36 nets.

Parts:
D1, D2, D3, D4, D5, D6, D7, D8, D9, D10, D11, D12, D13, D14, D15, D16, D17, D18, D19, D20, D21: DIODE; Diode-dual
ENC1: RotaryEncoder_Switch; RotaryEncoder_Alps_EC11E-Switch_Vertical_H20mm
JP1, JP2, JP3, JP4, JP5, JP6, JP7: SolderJumper_2_Open; SolderJumper-2_P1.3mm_Open_TrianglePad1.0x1.5mm
J_1_LEFT1, J_2_RIGHT1: RJ45_Shielded; RJ45_Ninigi_GE
K1, K2, K3, K4, K5, K6, K7, K8, K9, K10, K11, K12, K13, K14, K15, K16, K17, K18: SW_Push; Kailh_socket_MX_optional_reversible
U1: RP2040-Zero; MCU_RP2040_Zero_34

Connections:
COL_1: D21.1 (K), JP1.1 (A), K1.1, K2.1, K3.1, K4.1, K5.1, K6.1, U1.14 (GP14)
COL_2: D19.1 (K), JP2.1 (A), K7.1, K8.1, K9.1, K10.1, K11.1, K12.1, U1.15 (GP15)
COL_3: D20.1 (K), JP3.1 (A), K13.1, K14.1, K15.1, K16.1, K17.1, K18.1, U1.26 (GP26)
GND: J_1_LEFT1.1, J_1_LEFT1.SH, J_2_RIGHT1.1, J_2_RIGHT1.SH, U1.31 (GND)
unnamed: D1.1 (K), K1.2
unnamed: D2.1 (K), K2.2
unnamed: D3.1 (K), K3.2
unnamed: D4.2 (A), K4.2
unnamed: D5.2 (A), K5.2
unnamed: D6.2 (A), K6.2
unnamed: D7.1 (K), K7.2
unnamed: D8.1 (K), K8.2
unnamed: D9.1 (K), K9.2
unnamed: D10.2 (A), K10.2
unnamed: D11.2 (A), K11.2
unnamed: D12.2 (A), K12.2
unnamed: D13.1 (K), K13.2
unnamed: D14.1 (K), K14.2
unnamed: D15.1 (K), K15.2
unnamed: D16.2 (A), K16.2
unnamed: D17.2 (A), K17.2
unnamed: D18.2 (A), K18.2
unnamed: D19.2 (A), ENC1.A
unnamed: D20.2 (A), ENC1.B
unnamed: D21.2 (A), ENC1.S1
ROW_1: D1.2 (A), D4.1 (K), D7.2 (A), D10.1 (K), D13.2 (A), D16.1 (K), JP4.1 (A), U1.27 (GP27)
ROW_2: D2.2 (A), D5.1 (K), D8.2 (A), D11.1 (K), D14.2 (A), D17.1 (K), JP5.1 (A), U1.28 (GP28)
ROW_3: D3.2 (A), D6.1 (K), D9.2 (A), D12.1 (K), D15.2 (A), D18.1 (K), JP6.1 (A), U1.29 (GP29)
ROW_4: ENC1.C, ENC1.S2, JP7.1 (A), U1.8 (GP8)
R_COL_1: JP1.2 (B), J_1_LEFT1.2, J_2_RIGHT1.8, U1.0 (GP0)
R_COL_2: JP2.2 (B), J_1_LEFT1.3, J_2_RIGHT1.7, U1.1 (GP1)
R_COL_3: JP3.2 (B), J_1_LEFT1.4, J_2_RIGHT1.6, U1.2 (GP2)
R_ROW_1: JP4.2 (B), J_1_LEFT1.5, J_2_RIGHT1.5, U1.3 (GP3)
R_ROW_2: JP6.2 (B), J_1_LEFT1.6, J_2_RIGHT1.4, U1.4 (GP4)
R_ROW_3: JP5.2 (B), J_1_LEFT1.7, J_2_RIGHT1.3, U1.5 (GP5)
R_ROW_4: JP7.2 (B), J_1_LEFT1.8, J_2_RIGHT1.2, U1.6 (GP6)
